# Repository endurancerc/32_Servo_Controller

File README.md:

# 32_Servo_Controller
Firmware for the Endurance R/C 32 Servo Controller

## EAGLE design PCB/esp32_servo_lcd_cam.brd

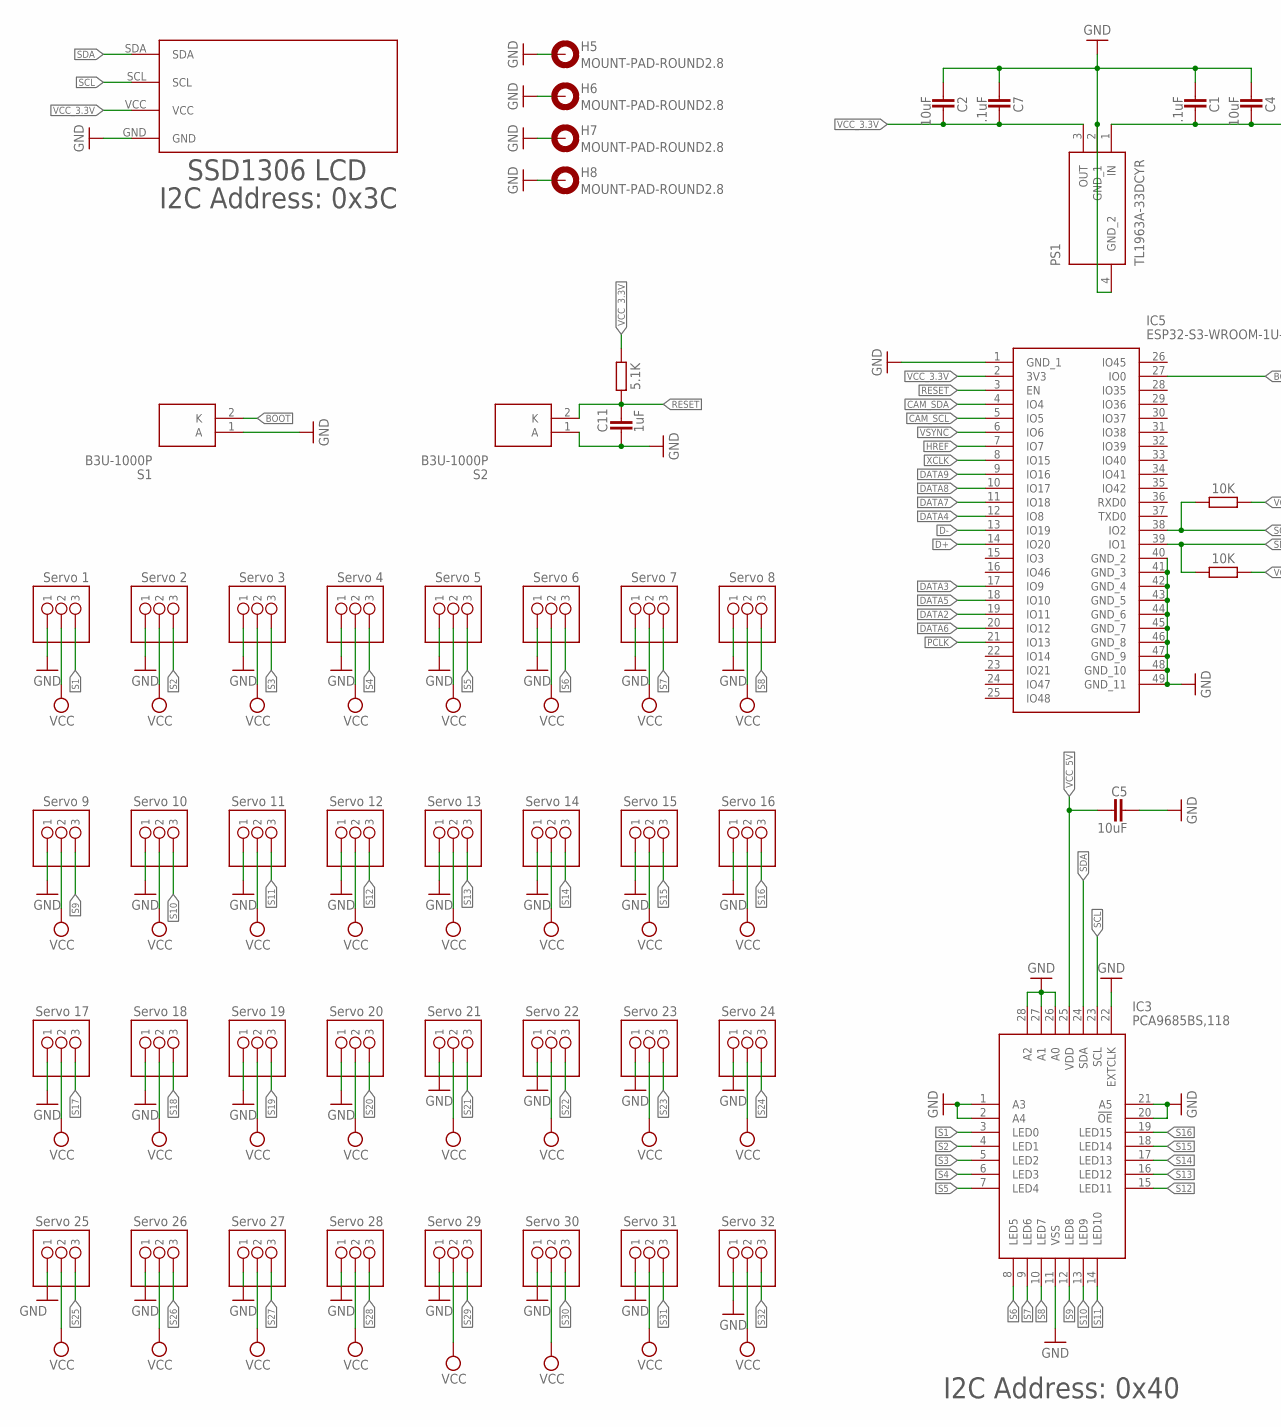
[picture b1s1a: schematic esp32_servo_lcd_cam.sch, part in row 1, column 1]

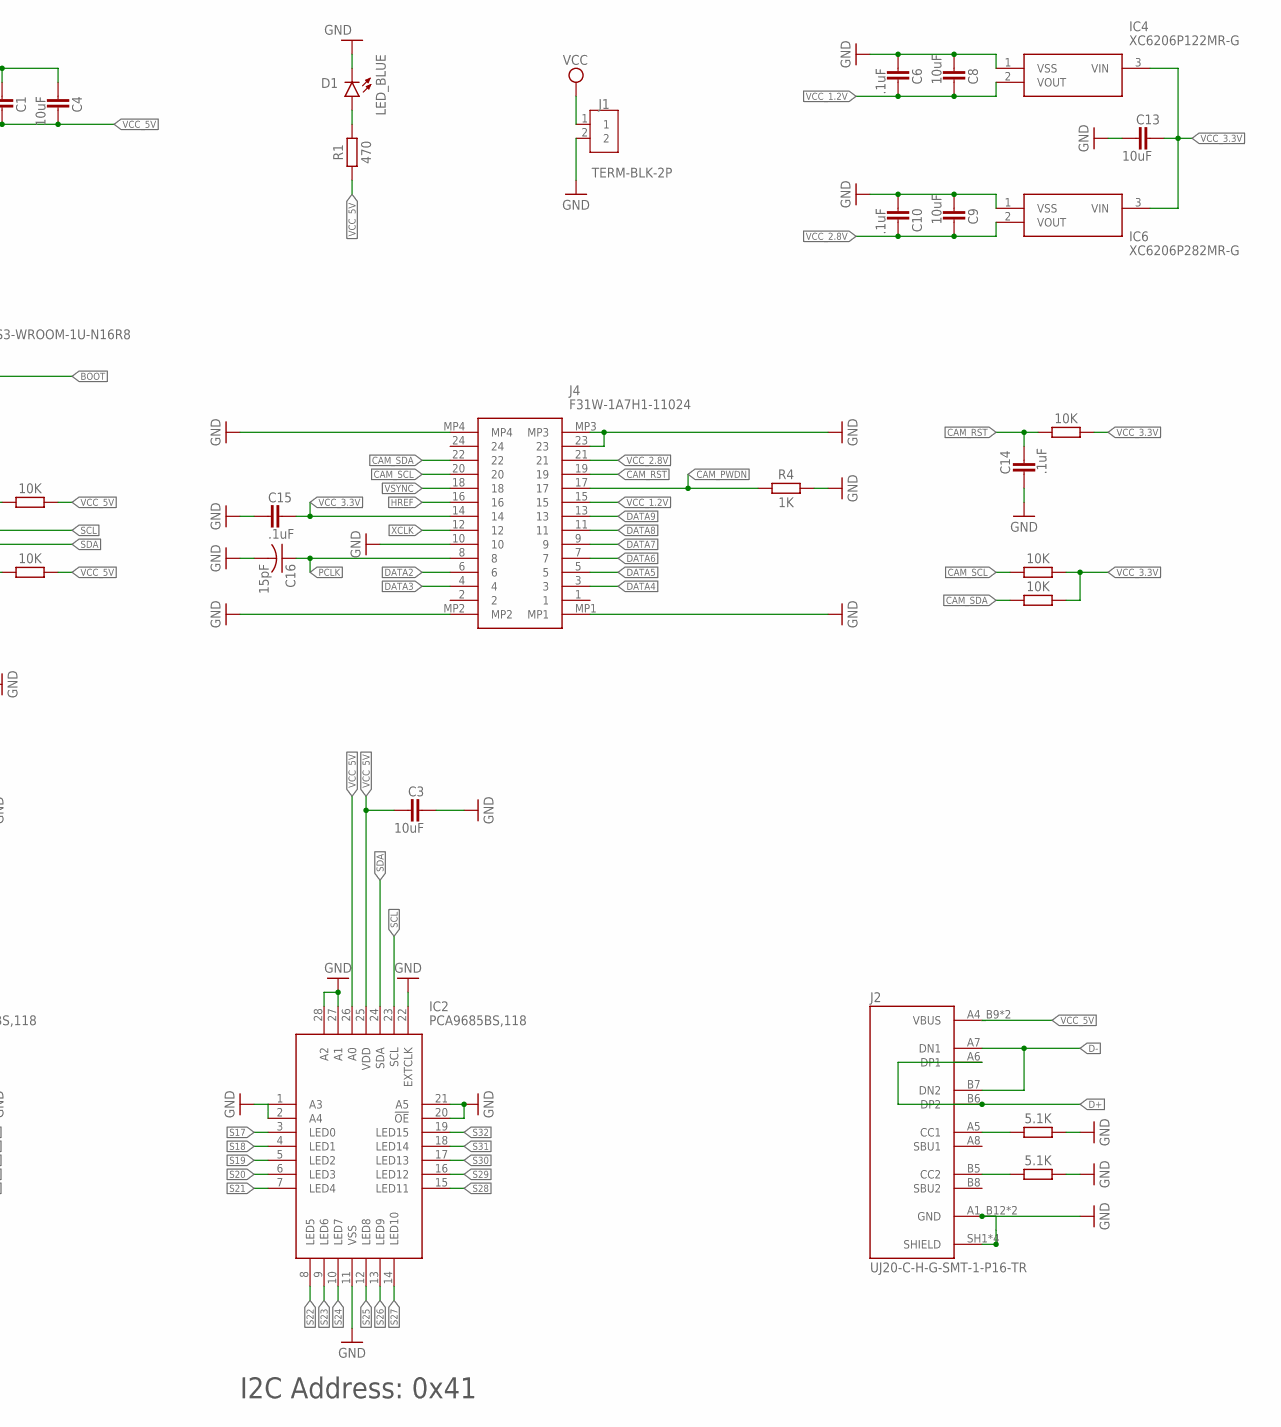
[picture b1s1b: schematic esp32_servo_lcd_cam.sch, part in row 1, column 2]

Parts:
C1, C6, C7, C10, C14, C15: .1uF; CAPC1110X102
C2, C3, C4, C5, C8, C9, C13: 10uF; CAPC1110X102
C11: 1uF; CAPC1110X102
C16: 15pF; CAPC2012X110
D1: LED_BLUE; LEDC1608X80N_FLAT-B
H5, H6, H7, H8: MOUNT-PAD-ROUND2.8; 2,8-PAD
IC2, IC3: PCA9685BS,118; QFN65P600X600X100-29N
IC4: XC6206P122MR-G; SOT95P280X130-3N
IC5: ESP32-S3-WROOM-1U-N16R8; ESP32S3WROOM1UN16R8
IC6: XC6206P282MR-G; SOT95P280X130-3N
J1: TERM-BLK-2P; TERMBLK_508-2N
J2: UJ20-C-H-G-SMT-1-P16-TR; SAMESKY_UJ20-C-H-G-SMT-1-P16-TR
J4: F31W-1A7H1-11024; F31W1A7H111024
PS1: TL1963A-33DCYR; SOT230P700X180-4N
R1: 470; RESC1005X40
R2, R11, R12: 5.1K; RESC1005X40
R3, R5, R6, R23, R24: 10K; RESC1005X40
R4: 1K; RESC1608X60
S1, S2: B3U-1000P
U$1: Servo 6; 1X03
U$2: Servo 7; 1X03
U$3: Servo 8; 1X03
U$4: Servo 9; 1X03
U$5: Servo 10; 1X03
U$6: Servo 11; 1X03
U$7: Servo 12; 1X03
U$8: Servo 13; 1X03
U$9: Servo 14; 1X03
U$10: Servo 15; 1X03
U$11: Servo 4; 1X03
U$12: Servo 5; 1X03
U$13: Servo 1; 1X03
U$14: Servo 3; 1X03
U$15: Servo 2; 1X03
U$16: Servo 16; 1X03
U$17: Servo 17; 1X03
U$18: Servo 18; 1X03
U$19: Servo 19; 1X03
U$20: Servo 21; 1X03
U$21: Servo 20; 1X03
U$22: Servo 22; 1X03
U$23: Servo 23; 1X03
U$24: Servo 24; 1X03
U$25: Servo 25; 1X03
U$26: Servo 26; 1X03
U$27: Servo 27; 1X03
U$28: Servo 28; 1X03
U$29: Servo 29; 1X03
U$30: Servo 30; 1X03
U$31: Servo 31; 1X03
U$32: Servo 32; 1X03
U$33: 128X32_SSD1306_I2C_LCD; 128X32_SSD1306_I2C_LCD_

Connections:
BOOT: IC5.27 (IO0), S1.2 (K)
CAM_PWDN: J4.17, R4.1
CAM_RST: C14.1, J4.19, R3.1
CAM_SCL: IC5.5 (IO5), J4.20, R5.1
CAM_SDA: IC5.4 (IO4), J4.22, R6.1
D+: IC5.14 (IO20), J2.A6 (DP1), J2.B6 (DP2)
D-: IC5.13 (IO19), J2.A7 (DN1), J2.B7 (DN2)
DATA2: IC5.19 (IO11), J4.6
DATA3: IC5.17 (IO9), J4.4
DATA4: IC5.12 (IO8), J4.3
DATA5: IC5.18 (IO10), J4.5
DATA6: IC5.20 (IO12), J4.7
DATA7: IC5.11 (IO18), J4.9
DATA8: IC5.10 (IO17), J4.11
DATA9: IC5.9 (IO16), J4.13
GND: C1.2, C2.2, C3.1, C4.2, C5.1, C6.2, C7.2, C8.2, C9.2, C10.2, C11.2, C13.2, C14.2, C15.2, C16.2, D1.C, H5.B2,8, H6.B2,8, H7.B2,8, H8.B2,8, IC2.11 (VSS), IC2.20 (!OE), IC2.21 (A5), IC2.27 (A1), IC2.28 (A2), IC3.1 (A3), IC3.2 (A4), IC3.11 (VSS), IC3.20 (!OE), IC3.21 (A5), IC3.22 (EXTCLK), IC3.26 (A0), IC3.27 (A1), IC3.28 (A2), IC4.1 (VSS), IC5.1 (GND_1), IC5.40 (GND_2), IC5.41 (GND_3), IC5.42 (GND_4), IC5.43 (GND_5), IC5.44 (GND_6), IC5.45 (GND_7), IC5.46 (GND_8), IC5.47 (GND_9), IC5.48 (GND_10), IC5.49 (GND_11), IC6.1 (VSS), J1.2, J2.A1_B12 (GND), J2.B1_A12 (GND), J2.SH1 (SHIELD), J2.SH2 (SHIELD), J2.SH3 (SHIELD), J2.SH4 (SHIELD), J4.10, J4.23, J4.MP1, J4.MP2, J4.MP3, J4.MP4, PS1.2 (GND_1), PS1.4 (GND_2), R4.2, R11.2, R12.2, S1.1 (A), S2.1 (A), U$1.1, U$2.1, U$3.1, U$4.1, U$5.1, U$6.1, U$7.1, U$8.1, U$9.1, U$10.1, U$11.1, U$12.1, U$13.1, U$14.1, U$15.1, U$16.1, U$17.1, U$18.1, U$19.1, U$20.1, U$21.1, U$22.1, U$23.1, U$24.1, U$25.1, U$26.1, U$27.1, U$28.1, U$29.1, U$30.1, U$31.1, U$32.1, U$33.GND
HREF: IC5.7 (IO7), J4.16
unnamed: D1.A, R1.2
unnamed: J2.A5 (CC1), R12.1
unnamed: J2.B5 (CC2), R11.1
PCLK: C16.1, IC5.21 (IO13), J4.8
RESET: C11.1, IC5.3 (EN), R2.2, S2.2 (K)
S1: IC3.3 (LED0), U$13.3
S2: IC3.4 (LED1), U$15.3
S3: IC3.5 (LED2), U$14.3
S4: IC3.6 (LED3), U$11.3
S5: IC3.7 (LED4), U$12.3
S6: IC3.8 (LED5), U$1.3
S7: IC3.9 (LED6), U$2.3
S8: IC3.10 (LED7), U$3.3
S9: IC3.12 (LED8), U$4.3
S10: IC3.13 (LED9), U$5.3
S11: IC3.14 (LED10), U$6.3
S12: IC3.15 (LED11), U$7.3
S13: IC3.16 (LED12), U$8.3
S14: IC3.17 (LED13), U$9.3
S15: IC3.18 (LED14), U$10.3
S16: IC3.19 (LED15), U$16.3
S17: IC2.3 (LED0), U$17.3
S18: IC2.4 (LED1), U$18.3
S19: IC2.5 (LED2), U$19.3
S20: IC2.6 (LED3), U$21.3
S21: IC2.7 (LED4), U$20.3
S22: IC2.8 (LED5), U$22.3
S23: IC2.9 (LED6), U$23.3
S24: IC2.10 (LED7), U$24.3
S25: IC2.12 (LED8), U$25.3
S26: IC2.13 (LED9), U$26.3
S27: IC2.14 (LED10), U$27.3
S28: IC2.15 (LED11), U$28.3
S29: IC2.16 (LED12), U$29.3
S30: IC2.17 (LED13), U$30.3
S31: IC2.18 (LED14), U$31.3
S32: IC2.19 (LED15), U$32.3
SCL: IC2.23 (SCL), IC3.23 (SCL), IC5.38 (IO2), R23.1, U$33.SCL
SDA: IC2.24 (SDA), IC3.24 (SDA), IC5.39 (IO1), R24.1, U$33.SDA
VCC: J1.1, U$1.2, U$2.2, U$3.2, U$4.2, U$5.2, U$6.2, U$7.2, U$8.2, U$9.2, U$10.2, U$11.2, U$12.2, U$13.2, U$14.2, U$15.2, U$16.2, U$17.2, U$18.2, U$19.2, U$20.2, U$21.2, U$22.2, U$23.2, U$24.2, U$25.2, U$26.2, U$27.2, U$28.2, U$29.2, U$30.2, U$31.2, U$32.2
VCC_1.2V: C6.1, C8.1, IC4.2 (VOUT), J4.15
VCC_2.8V: C9.1, C10.1, IC6.2 (VOUT), J4.21
VCC_3.3V: C2.1, C7.1, C13.1, C15.1, IC4.3 (VIN), IC5.2 (3V3), IC6.3 (VIN), J4.14, PS1.3 (OUT), R2.1, R3.2, R5.2, R6.2, U$33.VCC
VCC_5V: C1.1, C3.2, C4.1, C5.2, IC2.25 (VDD), IC2.26 (A0), IC3.25 (VDD), J2.A4_B9 (VBUS), J2.B4_A9 (VBUS), PS1.1 (IN), R1.1, R23.2, R24.2
VSYNC: IC5.6 (IO6), J4.18
XCLK: IC5.8 (IO15), J4.12

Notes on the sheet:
SSD1306 LCD
I2C Address: 0x40
I2C Address: 0x3C
I2C Address: 0x41

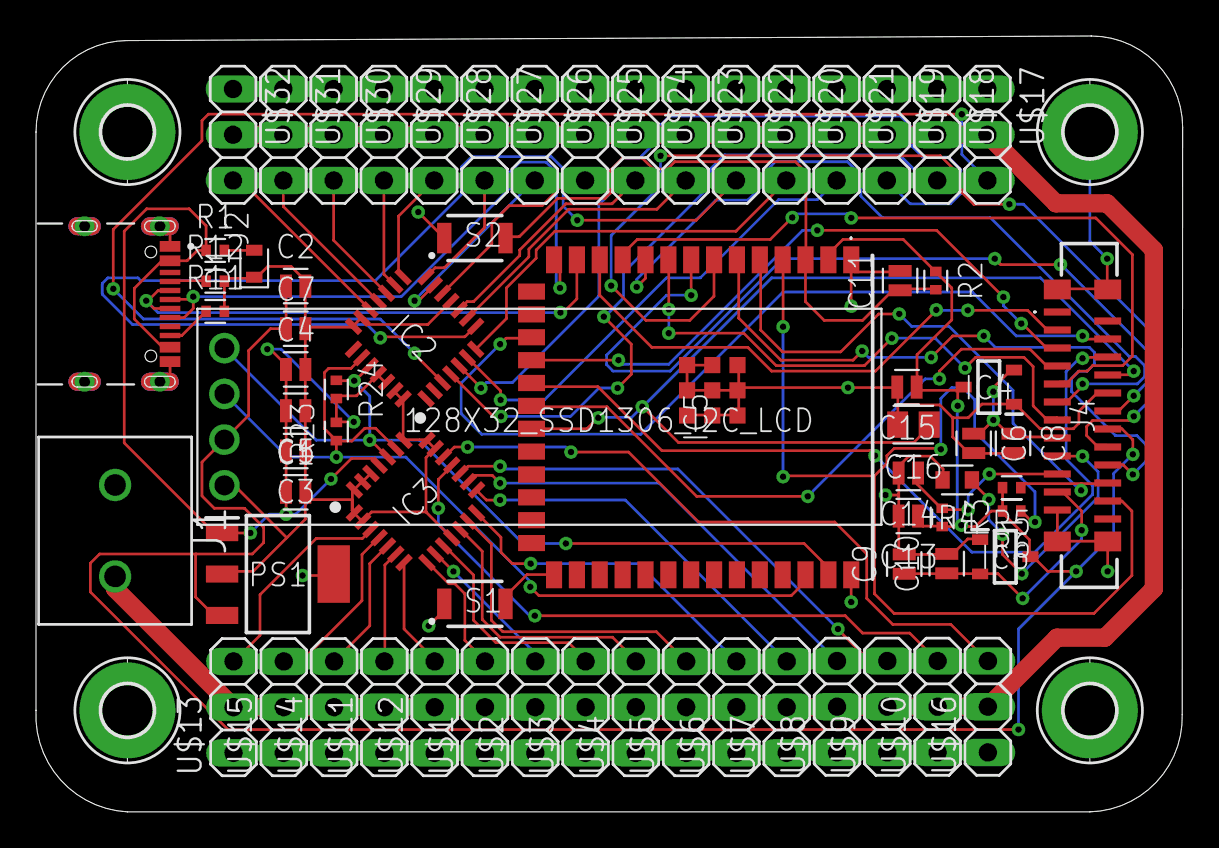
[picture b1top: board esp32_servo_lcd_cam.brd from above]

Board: 2 copper layers, 63.7 x 43.1 mm, 74 parts (0 on the bottom side), 63 nets.

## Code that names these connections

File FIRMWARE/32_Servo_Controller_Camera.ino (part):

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  function snapshot(){
    if(!_cameraPresent){log('No camera — snapshot unavailable','err');return;}
    fetch('/capture').then(r=>{if(!r.ok)throw 0;return r.blob();})
      .then(b=>{const a=document.createElement('a');a.href=URL.createObjectURL(b);
                a.download='snap_'+Date.now()+'.jpg';a.click();log('SNAPSHOT SAVED','ok');})
      .catch(()=>{log('SNAPSHOT FAILED','err');alert('Snapshot failed');});
  }
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    const ext=_recMime.startsWith('video/mp4')?'mp4':'webm';
    const blob=new Blob(_recChunks,{type:_recMime});
    const url=URL.createObjectURL(blob);
    const a=document.createElement('a');a.href=url;
    a.download='32sc_'+new Date().toISOString().slice(0,19).replace(/:/g,'-')+'.'+ext;
    document.body.appendChild(a);a.click();document.body.removeChild(a);
    URL.revokeObjectURL(url);_recChunks=[];
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  cfg.pin_d2       = Y4_GPIO_NUM;     cfg.pin_d3       = Y5_GPIO_NUM;
  cfg.pin_d4       = Y6_GPIO_NUM;     cfg.pin_d5       = Y7_GPIO_NUM;
  cfg.pin_d6       = Y8_GPIO_NUM;     cfg.pin_d7       = Y9_GPIO_NUM;
  cfg.pin_xclk     = XCLK_GPIO_NUM;   cfg.pin_pclk     = PCLK_GPIO_NUM;
  cfg.pin_vsync    = VSYNC_GPIO_NUM;  cfg.pin_href     = HREF_GPIO_NUM;
  cfg.pin_sscb_sda = SIOD_GPIO_NUM;   cfg.pin_sscb_scl = SIOC_GPIO_NUM;
  cfg.pin_pwdn     = PWDN_GPIO_NUM;   cfg.pin_reset    = RESET_GPIO_NUM;
  cfg.xclk_freq_hz = 20000000;
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  cfg.pin_d2       = Y4_GPIO_NUM;     cfg.pin_d3       = Y5_GPIO_NUM;
  cfg.pin_d4       = Y6_GPIO_NUM;     cfg.pin_d5       = Y7_GPIO_NUM;
  cfg.pin_d6       = Y8_GPIO_NUM;     cfg.pin_d7       = Y9_GPIO_NUM;
  cfg.pin_xclk     = XCLK_GPIO_NUM;   cfg.pin_pclk     = PCLK_GPIO_NUM;
  cfg.pin_vsync    = VSYNC_GPIO_NUM;  cfg.pin_href     = HREF_GPIO_NUM;
  cfg.pin_sscb_sda = SIOD_GPIO_NUM;   cfg.pin_sscb_scl = SIOC_GPIO_NUM;
  cfg.pin_pwdn     = PWDN_GPIO_NUM;   cfg.pin_reset    = RESET_GPIO_NUM;
  cfg.xclk_freq_hz = 20000000;
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
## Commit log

2026-05-15 Create temp
